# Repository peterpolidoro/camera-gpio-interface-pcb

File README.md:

# camera-gpio-interface-pcb

Interface board for the three FLIR Blackfly S cameras in the Janelia Dudman lab
joystick rig: pluggable screw-terminal camera connectors, two BNC inputs from
the pyControl breakout, four 3.3 V BNC outputs to a Neuropixels OneBox, an
InstrumentPort-Digital-50 with every camera line tapped, and USB power. No
MCU, no firmware, no configuration jumpers.

**Status, October 2026:** v1.0 is the fabricated revision. Five assembled
boards were ordered from JLCPCB on 2026-09-26
([fabrication log](docs/fabrication-log.md)), and one is installed in the
rig, wired to the three cameras, the pyControl breakout and the OneBox. Bench
results per board go in [the bring-up log](docs/bringup-log.md).

## The Board

The block below is written by `make docs` from the KiCad sources: renders, key
dimensions, and links to the schematic, BOM, STEP model and enclosure geometry.
Do not edit between the markers; run `make docs` instead.

<!-- BEGIN GENERATED BOARD DOCUMENTATION -->
<!-- Generated by orb-weaver-kicad-docs. Edits between these markers are lost. -->

More views, including both elevations, are in [the generated documentation](docs/generated/README.md).

The documentation site, with the board turning and its design blocks clickable: [https://peterpolidoro.github.io/camera-gpio-interface-pcb/](https://peterpolidoro.github.io/camera-gpio-interface-pcb/).

| Property | Value |
| --- | --- |
| Outline | 100.0 × 60.0 mm, 5.0 mm corner radius |
| Thickness | 1.6 mm |
| Copper layers | 4 |
| Mounting holes | 4 × 3.2 mm |
| Connectors and controls | 11 |
| Bill of materials | 26 distinct parts, 151 placements |

### Documents

| Document | File |
| --- | --- |
| Schematic, all sheets, PDF | [camera-gpio-interface-pcb-schematic.pdf](docs/generated/schematic/camera-gpio-interface-pcb-schematic.pdf) |
| Schematic sheets, SVG (11) | [schematic/](docs/generated/schematic/) |
| Schematic, instance overviews and details, PDF | [Review booklet](docs/generated/schematic/camera-gpio-interface-pcb-schematic-review.pdf) |
| Design blocks placed (7), one page each | [blocks/README.md](docs/generated/blocks/README.md) |
| Board view: the model and the top render with the design blocks numbered | [board-view.md](docs/generated/board-view.md) |
| Subsystem sheets (3), from their recipes | [subsystems/README.md](docs/generated/subsystems/README.md) |
| Assembly view, top | [assembly-top.svg](docs/generated/layout/assembly-top.svg) |
| Assembly view, bottom | [assembly-bottom.svg](docs/generated/layout/assembly-bottom.svg) |
| Assembled board, STEP, for FreeCAD | [camera-gpio-interface-pcb-assembled.step](docs/generated/3d/camera-gpio-interface-pcb-assembled.step) |
| Assembled board, glTF, for a viewer (the library's materials written in) | [camera-gpio-interface-pcb.glb](docs/generated/3d/camera-gpio-interface-pcb.glb) |
| Bill of materials | [table](docs/generated/bom/camera-gpio-interface-pcb-bom.md) · [CSV](docs/generated/bom/camera-gpio-interface-pcb-bom.csv) |
| Outline and mounting holes, dimensioned drawing | [SVG](docs/generated/mechanical/board-dimensions.svg) · [PDF](docs/generated/mechanical/board-dimensions.pdf) · [PNG](docs/generated/mechanical/board-dimensions.png) |
| Board dimensions and stackup | [board-dimensions.md](docs/generated/mechanical/board-dimensions.md) |
| Board geometry, machine readable | [board-geometry.json](docs/generated/mechanical/board-geometry.json) |
| Mounting holes | [mounting-holes.csv](docs/generated/mechanical/mounting-holes.csv) |
| Connector locations | [connectors.csv](docs/generated/mechanical/connectors.csv) |

### Enclosure Reference

Millimetres from the **centre of the board outline**, X right and Y up,
looking at the top of the board. Extents are the part's courtyard, which is
what a panel cutout has to clear. Full tables in [board-dimensions.md](docs/generated/mechanical/board-dimensions.md).

The outline and the mounting holes dimensioned, as KiCad draws them: [SVG](docs/generated/mechanical/board-dimensions.svg) · [PDF](docs/generated/mechanical/board-dimensions.pdf); the cross is the centre the tables measure from.

**Mounting holes**

| Ref | X (mm) | Y (mm) | Drill (mm) |
| --- | --- | --- | --- |
| H101 | -45.0 | 25.0 | 3.2 |
| H102 | 45.0 | 25.0 | 3.2 |
| H103 | 45.0 | -25.0 | 3.2 |
| H104 | -45.0 | -25.0 | 3.2 |

**Connectors and controls**

| Ref | Part | X (mm) | Y (mm) | Rot | Extent X (mm) | Extent Y (mm) |
| --- | --- | --- | --- | --- | --- | --- |
| J301 | HL-BNC-KHDA | -24.0 | -23.0 | 0.0 | -30.5 to -17.5 | -29.5 to -16.5 |
| J302 | HL-BNC-KHDA | 0.0 | -23.0 | 0.0 | -6.5 to 6.5 | -29.5 to -16.5 |
| J401 | HL-BNC-KHDA | 24.0 | -23.0 | 0.0 | 17.5 to 30.5 | -29.5 to -16.5 |
| J402 | HL-BNC-KHDA | -24.0 | 1.0 | 0.0 | -30.5 to -17.5 | -5.5 to 7.5 |
| J403 | HL-BNC-KHDA | 0.0 | 1.0 | 0.0 | -6.5 to 6.5 | -5.5 to 7.5 |
| J404 | HL-BNC-KHDA | 24.0 | 1.0 | 0.0 | 17.5 to 30.5 | -5.5 to 7.5 |
| J501 | FH12-50S-0.5SVA(54) | 44.0 | -4.0 | 270.0 | 41.2 to 46.8 | -18.75 to 10.75 |
| J701 | TBH-1x06-3.5mm | -25.0 | 24.0 | 180.0 | -36.7 to -13.3 | 19.25 to 27.5 |
| J901 | USB-C | -44.0 | 1.0 | 90.0 | -46.31 to -41.69 | -4.05 to 6.05 |
| J1201 | TBH-1x06-3.5mm | 0.0 | 24.0 | 180.0 | -11.7 to 11.7 | 19.25 to 27.5 |
| J1401 | TBH-1x06-3.5mm | 25.0 | 24.0 | 180.0 | 13.3 to 36.7 | 19.25 to 27.5 |

<!-- END GENERATED BOARD DOCUMENTATION -->

## Documents

- [Interface map](docs/interface-map.md): what each connector and instrument-port channel carries
- [Rev 0 plan](docs/rev0-plan.md): the design record
- [Fabrication log](docs/fabrication-log.md): what was ordered, from which commit, with which package hashes
- [Bring-up log](docs/bringup-log.md): bench results per board serial
- [Generated board documentation](docs/generated/README.md): schematic PDF and SVGs, renders, STEP and glTF, BOM, enclosure geometry and the dimensioned outline drawing, one page per placed design block and per subsystem sheet, rebuilt from the KiCad sources
- [The documentation site](https://peterpolidoro.github.io/camera-gpio-interface-pcb/): the same pages with the board turning and its design blocks clickable

## Fabrication

The v1.0 boards were ordered assembled from JLCPCB from the package built at
commit `5ddb425`. [The fabrication log](docs/fabrication-log.md) records the
commit, the source hashes and the hash of every file JLCPCB received.
[fab/camera-gpio-interface-pcb/](fab/camera-gpio-interface-pcb/) holds the
package rebuilt from the same sources on 2026-10-12: upload
`camera-gpio-interface-pcb-jlcpcb.zip`, `jlcpcb-bom.csv` and
`jlcpcb-camera-gpio-interface-pcb-all-pos.csv` to order more boards. The BOM
and placement files are byte-identical to the uploaded ones; the gerbers
differ only by the creation time in their headers. To fabricate elsewhere,
plot the layers and drill files from `kicad/camera-gpio-interface-pcb.kicad_pcb`
in KiCad. JLCPCB's placement rotation differs from KiCad's for some
footprints, so check the assembly preview before confirming an order.

## Related Repositories

- [mouse-joystick-pcb](https://github.com/peterpolidoro/mouse-joystick-pcb): the rig's joystick controller board.
- [mouse-joystick-firm](https://github.com/peterpolidoro/mouse-joystick-firm): its firmware and the pyControl device class.
- [mouse-joysticks-mech](https://github.com/peterpolidoro/mouse-joysticks-mech): the two-joystick mechanical assembly, part by part, with [the atlas site](https://peterpolidoro.github.io/mouse-joysticks-mech/) and the PDF manual of the whole rig.
- [joystick-rig](https://github.com/sourishmukh/joystick-rig): the rig's pyControl tasks, hardware definition and operating notes.

## Development

Opening, editing and fabricating the board needs only KiCad 10; the schematic
and board carry their own copies of every symbol and footprint. The board was
drawn from a shared KiCad library and toolchain, which is needed only to
regenerate `docs/generated/`, the fabrication package or the composed sheets.
[docs/development.md](docs/development.md) describes that toolchain, the
environment, the sibling repositories and the layout record. Agent guidance is
in `AGENTS.md` and `.agents/`.

## License

Hardware design files and documentation are CC-BY-SA-4.0; code and automation
are 3-clause BSD. See [LICENSE](LICENSE).

## Citation

[CITATION.cff](CITATION.cff) carries the citation metadata; GitHub renders it
under "Cite this repository".

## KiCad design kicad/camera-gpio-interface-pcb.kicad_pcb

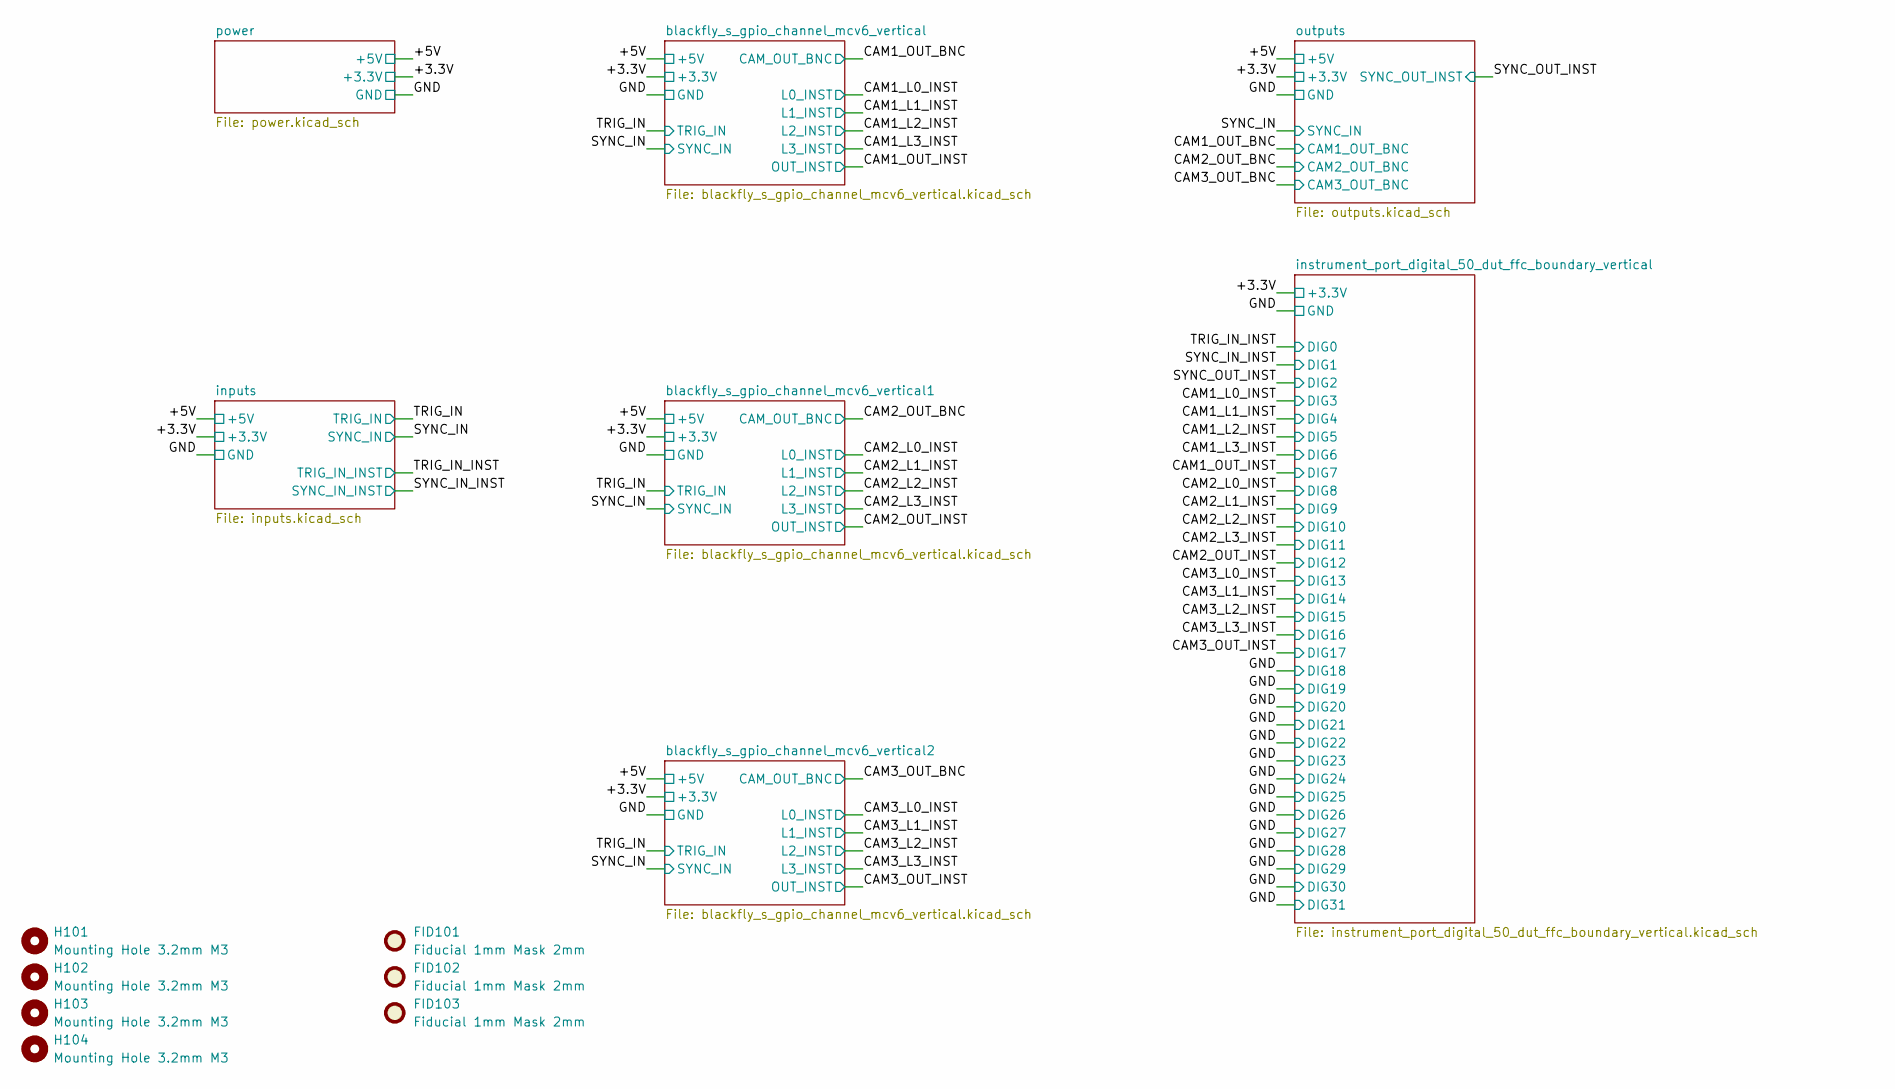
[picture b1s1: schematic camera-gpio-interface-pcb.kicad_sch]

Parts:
FID101, FID102, FID103: Fiducial 1mm Mask 2mm; Fiducial_1mm_Mask2mm
H101, H102, H103, H104: Mounting Hole 3.2mm M3; MountingHole_3.2mm_M3

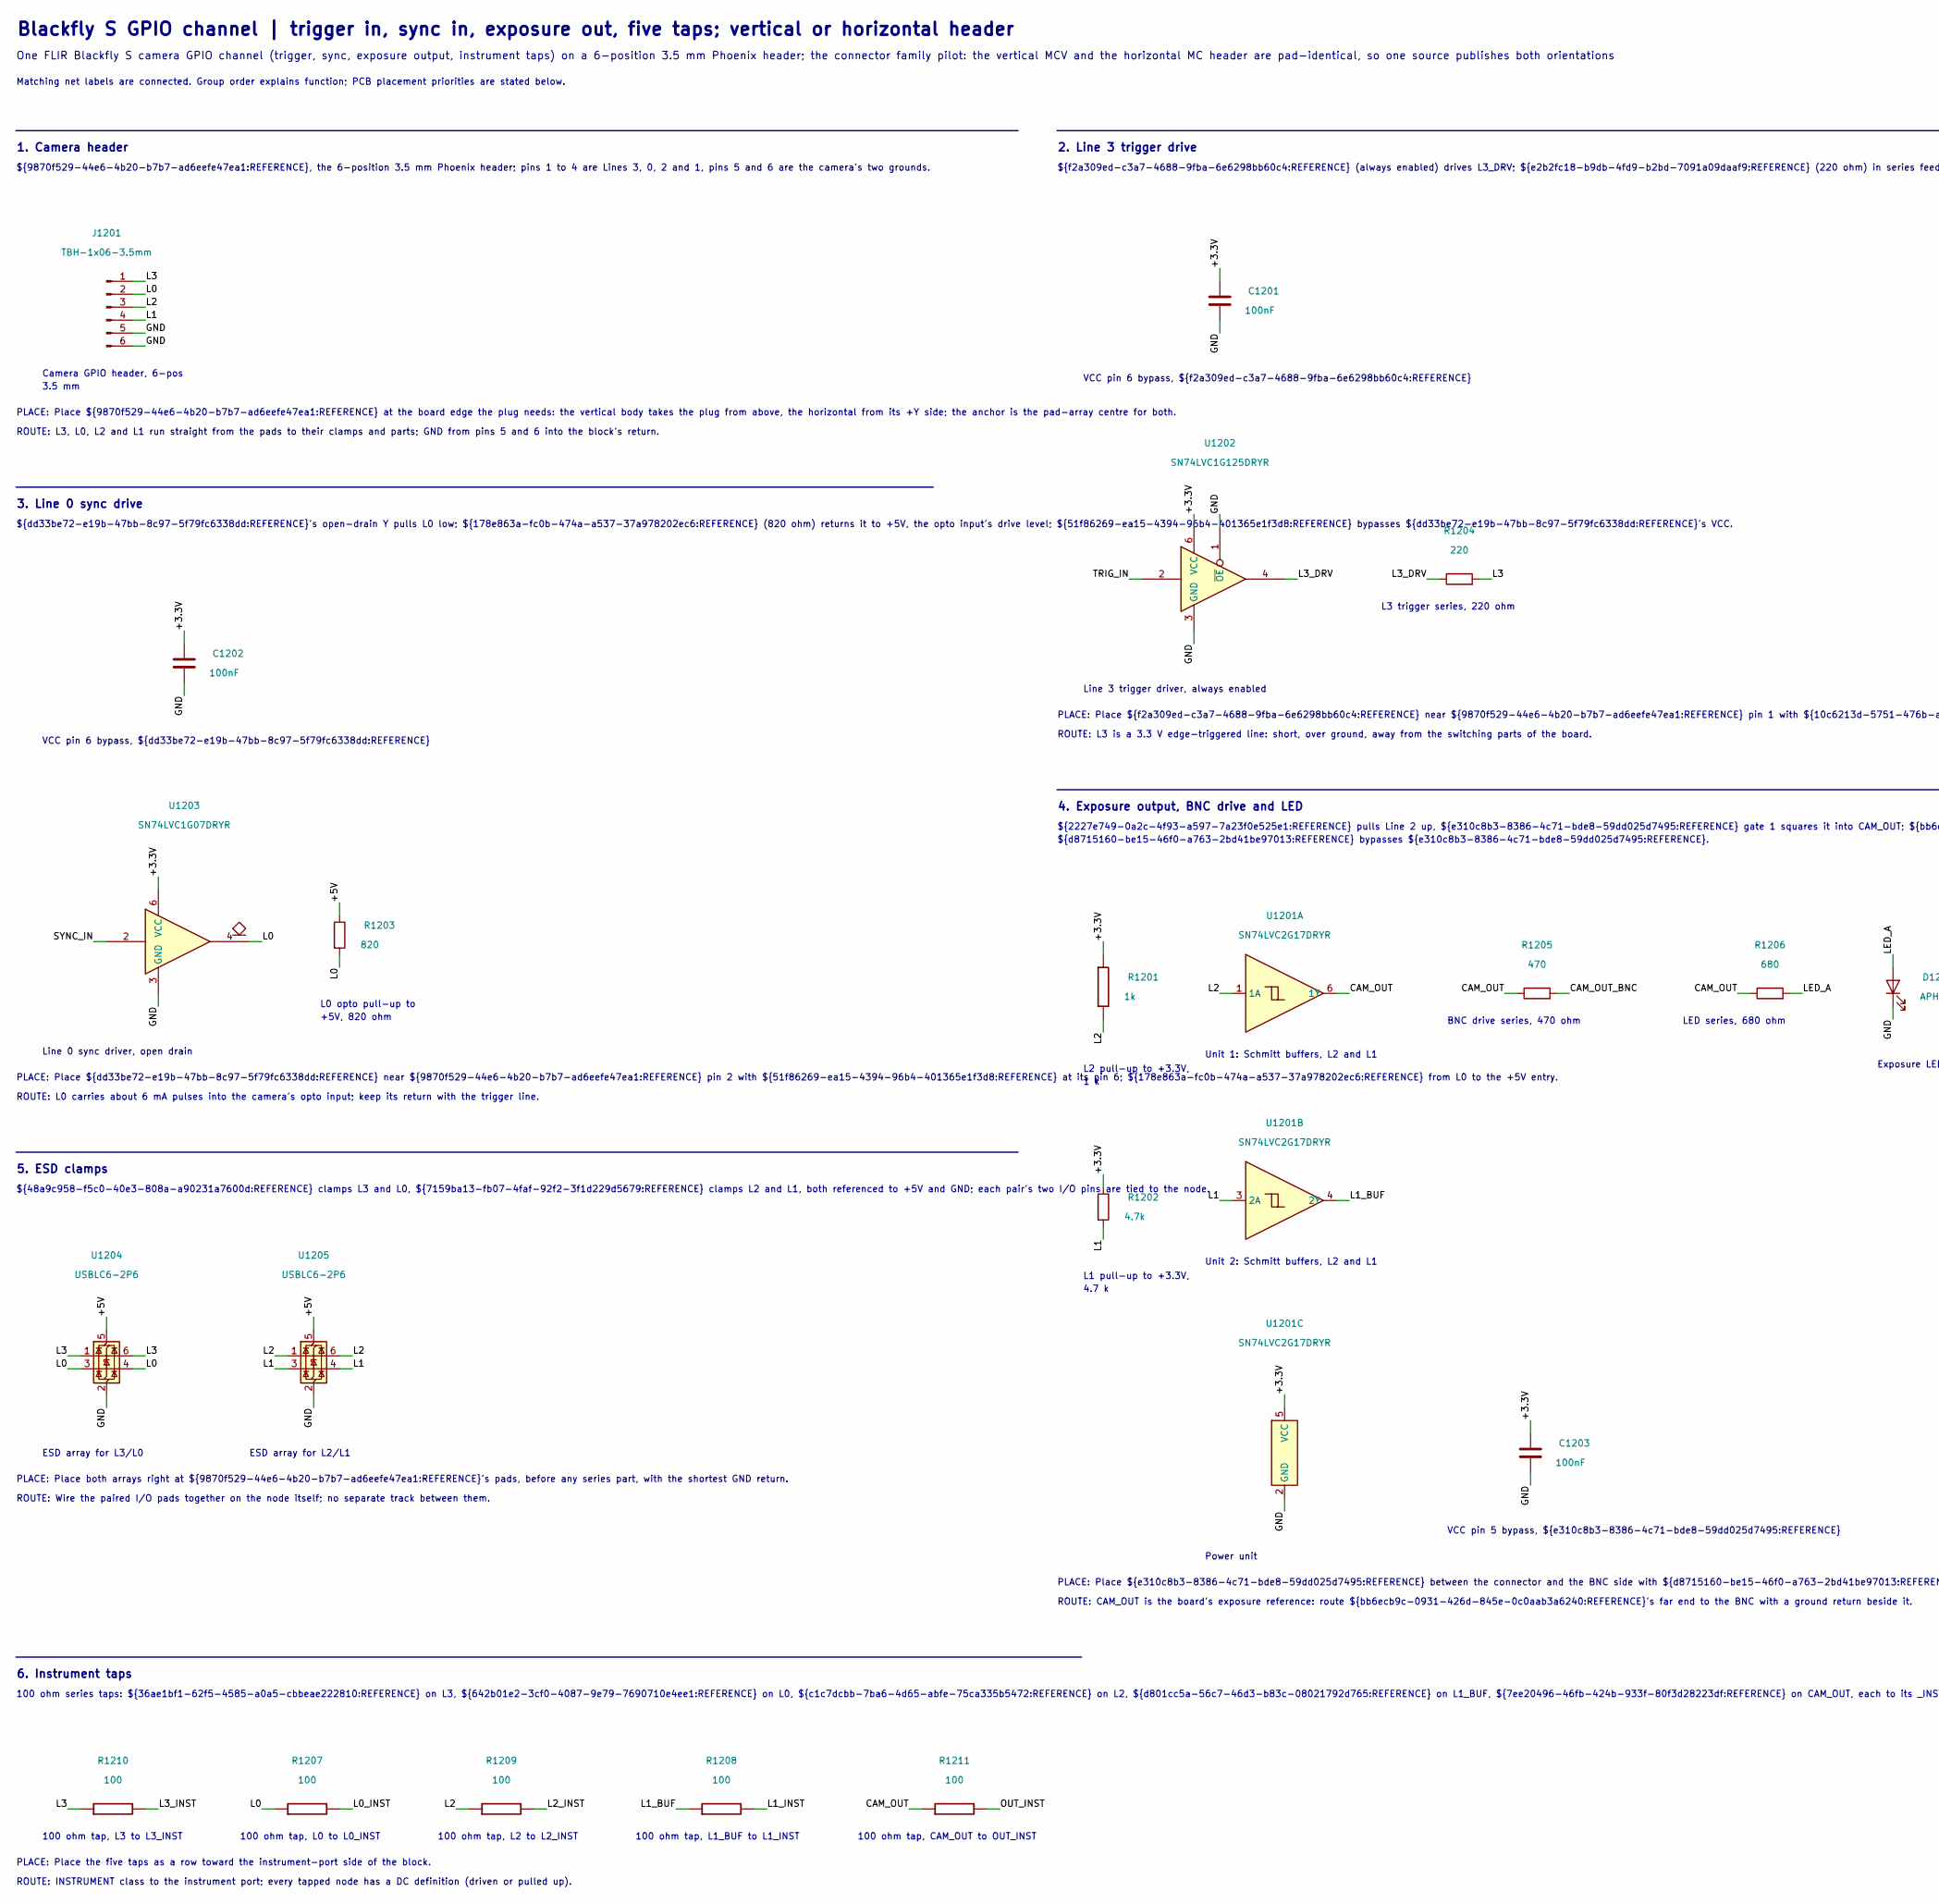
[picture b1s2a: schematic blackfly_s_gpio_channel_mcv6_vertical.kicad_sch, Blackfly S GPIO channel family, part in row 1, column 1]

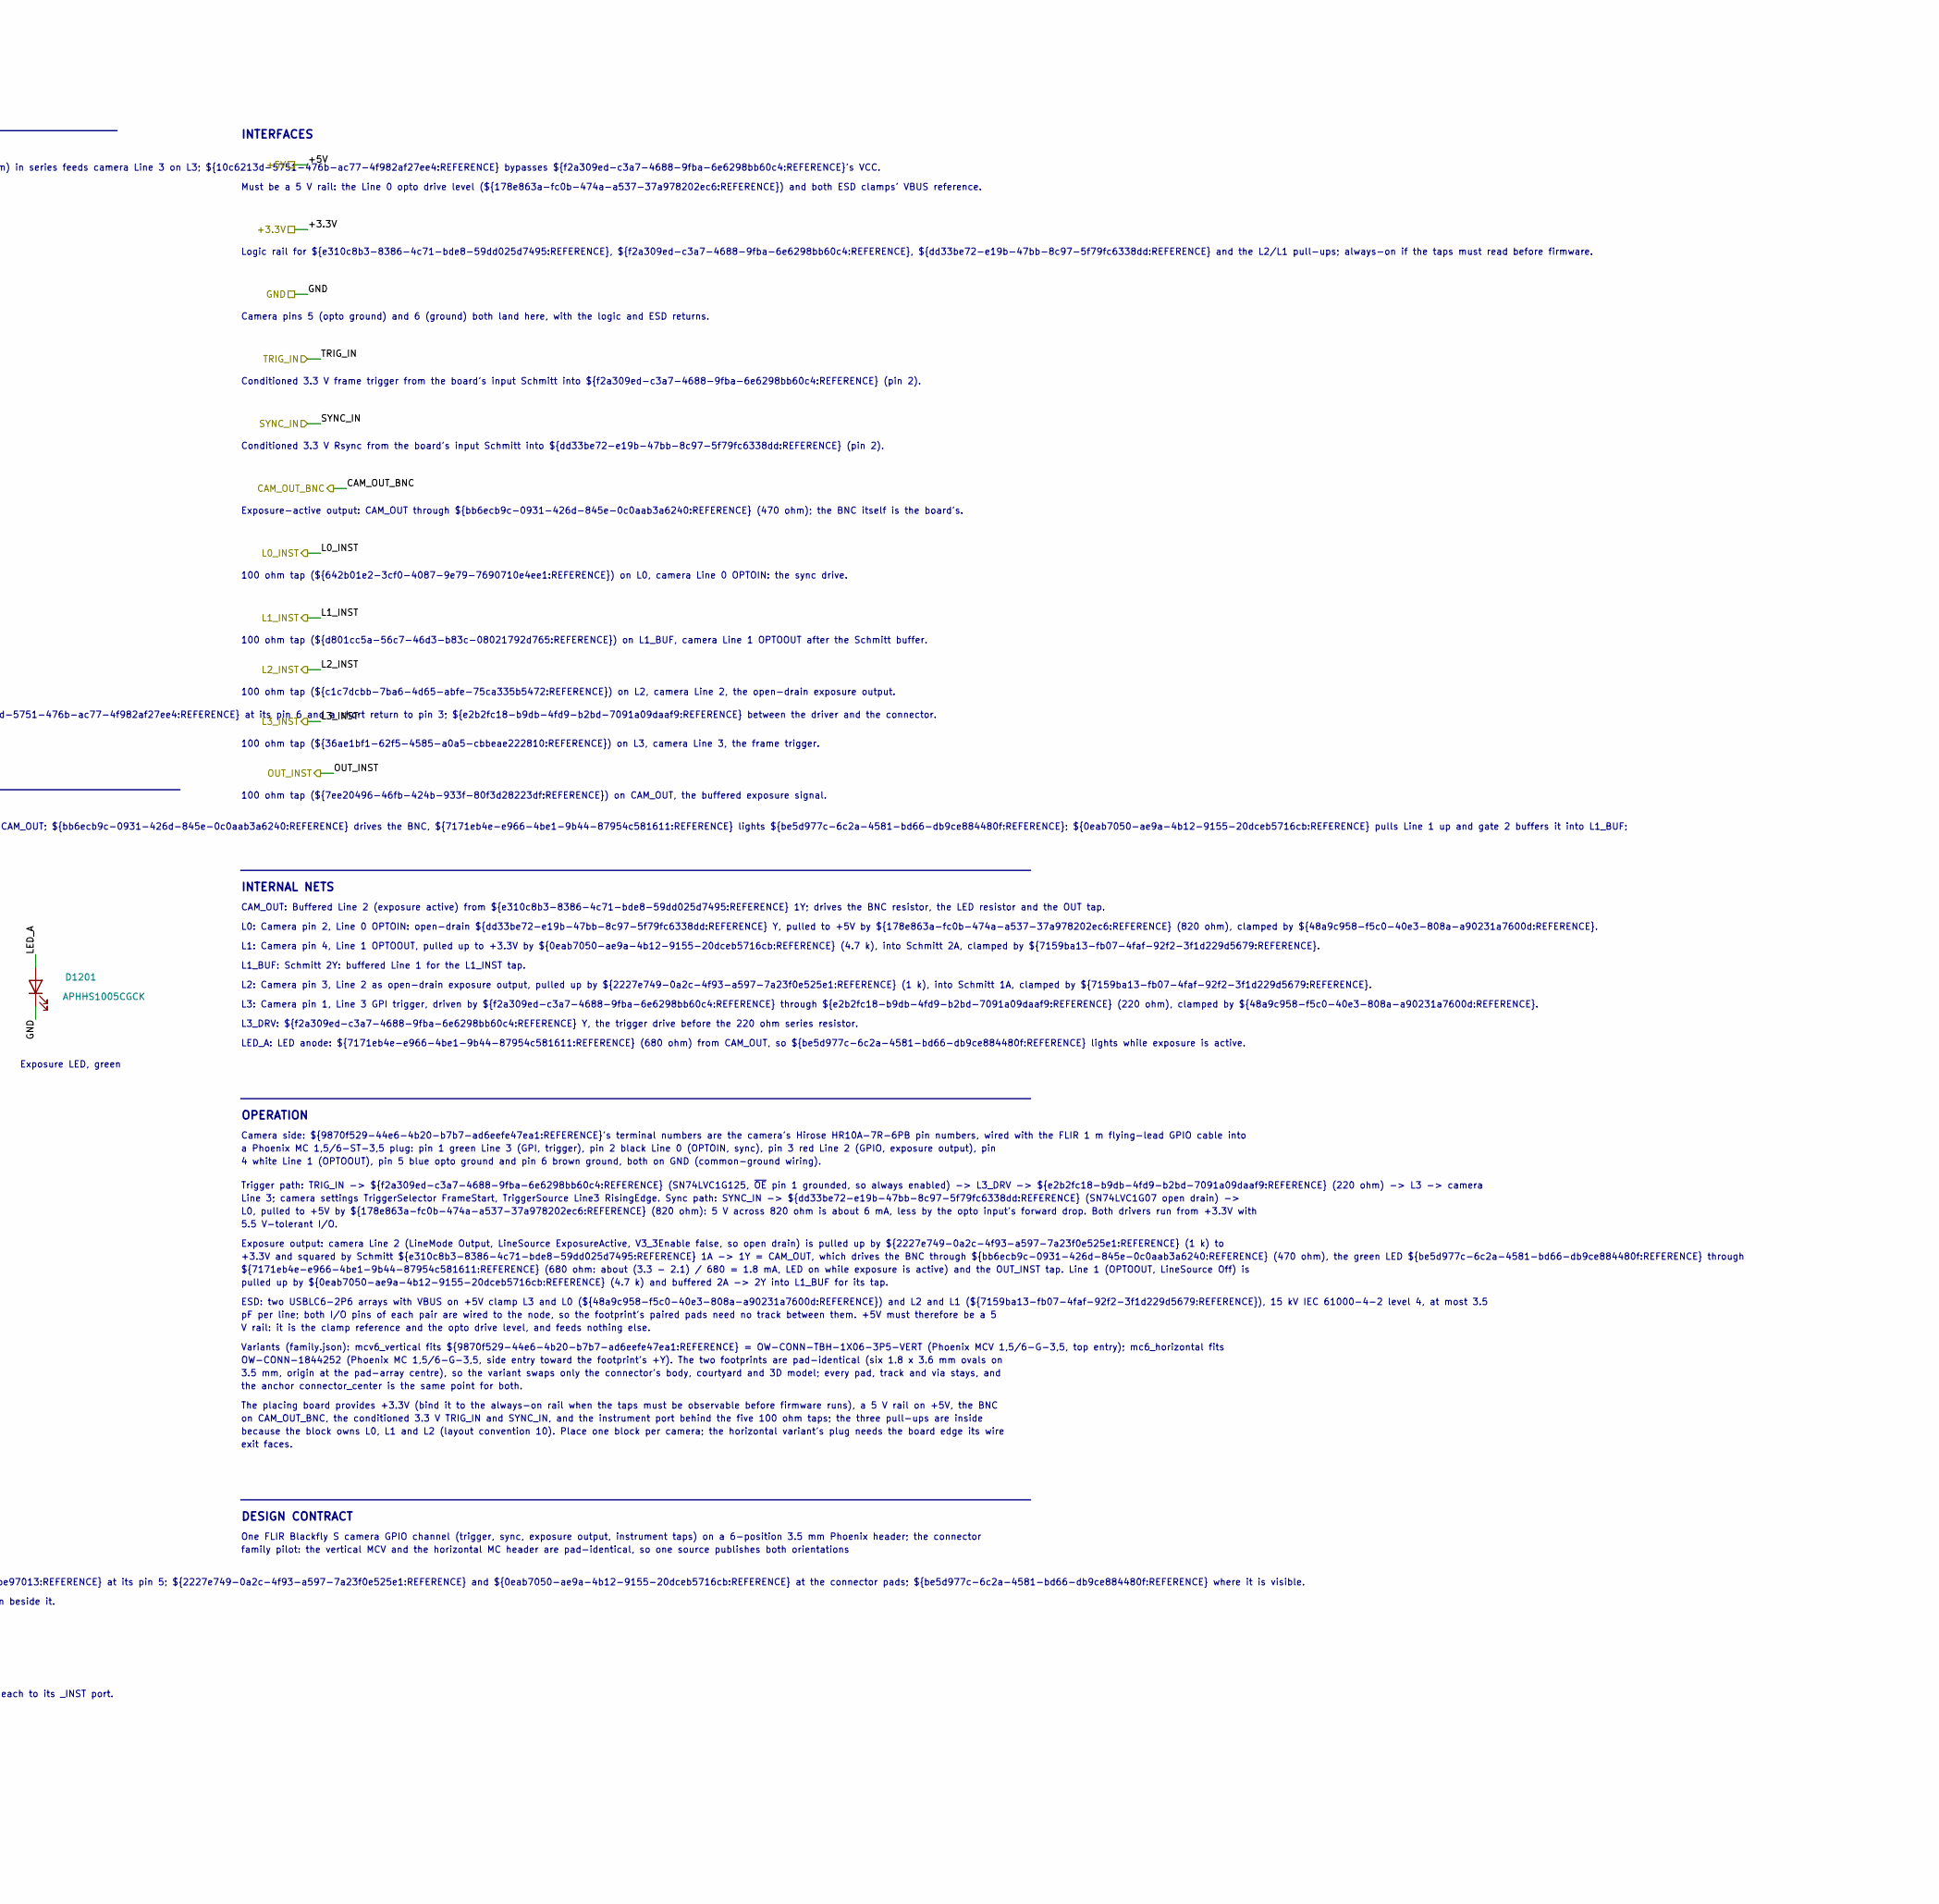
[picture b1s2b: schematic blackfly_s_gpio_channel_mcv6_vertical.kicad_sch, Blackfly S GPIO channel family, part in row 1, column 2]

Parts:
C1201, C1202, C1203: 100nF; C_0402_1005Metric; PartID sym_orb_weaver_passives_c_0_1uf_100v_04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
D1201: APHHS1005CGCK; LED_0402-1005_KNB; PartID sym_orb_weaver_misc_led_knb_20ma_grn_2_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
J1201: TBH-1x06-3.5mm; PhoenixContact_MCV_1,5_6-G-3.5_1x06_P3.50mm_Vertical; PartID sym_orb_weaver_connectors_conn_01x06_p3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
R1201: 1k; R_0402_1005Metric; PartID sym_orb_weaver_passives_r_1k_0402
R1202: 4.7k; R_0402_1005Metric; PartID sym_orb_weaver_passives_r_4_7k_0402
R1203: 820; R_0402_1005Metric; PartID mpn_frc0402f8200ts_0402
R1204: 220; R_0603_1608Metric; PartID mpn_0603waf2200t5e_0603
R1205: 470; R_0603_1608Metric; PartID mpn_0603waf4700t5e_0603
R1206: 680; R_0402_1005Metric; PartID mpn_rc0402fr_07680rl_0402
R1207, R1208, R1209, R1210, R1211: 100; R_0402_1005Metric; PartID sym_orb_weaver_passives_r_100_0402
U1201: SN74LVC2G17DRYR; DRY6; PartID sym_orb_weaver_misc_buffer_74lvc2g17dryr
U1202: SN74LVC1G125DRYR; DRY6; PartID sym_orb_weaver_misc_buffer_74lvc1g125dr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
U1203: SN74LVC1G07DRYR; DRY6; PartID sym_orb_weaver_misc_buffer_74lvc1g07dryr
U1204, U1205: USBLC6-2P6; USBLC6-2P6_SOT-666; PartID mpn_usblc6_2p6_sot_666_6

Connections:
/+3.3V: C1201.1, C1202.1, C1203.1, R1201.1, R1202.1, U1201.5 (VCC), U1202.6 (VCC), U1203.6 (VCC); also elsewhere on the board
/+5V: R1203.1, U1204.5 (VBUS), U1205.5 (VBUS); also elsewhere on the board
/CAM2_L0_INST: R1207.2; also elsewhere on the board
/CAM2_L1_INST: R1208.2; also elsewhere on the board
/CAM2_L2_INST: R1209.2; also elsewhere on the board
/CAM2_L3_INST: R1210.2; also elsewhere on the board
/CAM2_OUT_BNC: R1205.2; also elsewhere on the board
/CAM2_OUT_INST: R1211.2; also elsewhere on the board
/GND: C1201.2, C1202.2, C1203.2, D1201.1 (K), J1201.5, J1201.6, U1201.2 (GND), U1202.1 (~OE), U1202.3 (GND), U1203.3 (GND), U1204.2 (GND), U1205.2 (GND); also elsewhere on the board
/SYNC_IN: U1203.2; also elsewhere on the board
/TRIG_IN: U1202.2; also elsewhere on the board
/blackfly_s_gpio_channel_mcv6_vertical1/CAM_OUT: R1205.1, R1206.1, R1211.1, U1201.6 (1Y)
/blackfly_s_gpio_channel_mcv6_vertical1/L0: J1201.2, R1203.2, R1207.1, U1203.4, U1204.3 (I/O2), U1204.4 (I/O2)
/blackfly_s_gpio_channel_mcv6_vertical1/L1: J1201.4, R1202.2, U1201.3 (2A), U1205.3 (I/O2), U1205.4 (I/O2)
/blackfly_s_gpio_channel_mcv6_vertical1/L1_BUF: R1208.1, U1201.4 (2Y)
/blackfly_s_gpio_channel_mcv6_vertical1/L2: J1201.3, R1201.2, R1209.1, U1201.1 (1A), U1205.1 (I/O1), U1205.6 (I/O1)
/blackfly_s_gpio_channel_mcv6_vertical1/L3: J1201.1, R1204.2, R1210.1, U1204.1 (I/O1), U1204.6 (I/O1)
/blackfly_s_gpio_channel_mcv6_vertical1/L3_DRV: R1204.1, U1202.4
/blackfly_s_gpio_channel_mcv6_vertical1/LED_A: D1201.2 (A), R1206.2

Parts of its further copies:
C701, C702, C703, C1401, C1402, C1403: 100nF; C_0402_1005Metric; PartID sym_orb_weaver_passives_c_0_1uf_100v_04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
D701, D1401: APHHS1005CGCK; LED_0402-1005_KNB; PartID sym_orb_weaver_misc_led_knb_20ma_grn_2_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
J701, J1401: TBH-1x06-3.5mm; PhoenixContact_MCV_1,5_6-G-3.5_1x06_P3.50mm_Vertical; PartID sym_orb_weaver_connectors_conn_01x06_p3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
R701, R1401: 1k; R_0402_1005Metric; PartID sym_orb_weaver_passives_r_1k_0402
R702, R1402: 4.7k; R_0402_1005Metric; PartID sym_orb_weaver_passives_r_4_7k_0402
R703, R1403: 820; R_0402_1005Metric; PartID mpn_frc0402f8200ts_0402
R704, R1404: 220; R_0603_1608Metric; PartID mpn_0603waf2200t5e_0603
R705, R1405: 470; R_0603_1608Metric; PartID mpn_0603waf4700t5e_0603
R706, R1406: 680; R_0402_1005Metric; PartID mpn_rc0402fr_07680rl_0402
R707, R708, R709, R710, R711, R1407, R1408, R1409, R1410, R1411: 100; R_0402_1005Metric; PartID sym_orb_weaver_passives_r_100_0402
U701, U1401: SN74LVC2G17DRYR; DRY6; PartID sym_orb_weaver_misc_buffer_74lvc2g17dryr
U702, U1402: SN74LVC1G125DRYR; DRY6; PartID sym_orb_weaver_misc_buffer_74lvc1g125dr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
U703, U1403: SN74LVC1G07DRYR; DRY6; PartID sym_orb_weaver_misc_buffer_74lvc1g07dryr
U704, U705, U1404, U1405: USBLC6-2P6; USBLC6-2P6_SOT-666; PartID mpn_usblc6_2p6_sot_666_6

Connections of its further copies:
/+3.3V: C701.1, C702.1, C703.1, C1401.1, C1402.1, C1403.1, R701.1, R702.1, R1401.1, R1402.1, U701.5 (VCC), U702.6 (VCC), U703.6 (VCC), U1401.5 (VCC), U1402.6 (VCC), U1403.6 (VCC); also elsewhere on the board
/+5V: R703.1, R1403.1, U704.5 (VBUS), U705.5 (VBUS), U1404.5 (VBUS), U1405.5 (VBUS); also elsewhere on the board
/CAM1_L0_INST: R707.2; also elsewhere on the board
/CAM1_L1_INST: R708.2; also elsewhere on the board
/CAM1_L2_INST: R709.2; also elsewhere on the board
/CAM1_L3_INST: R710.2; also elsewhere on the board
/CAM1_OUT_BNC: R705.2; also elsewhere on the board
/CAM1_OUT_INST: R711.2; also elsewhere on the board
/CAM3_L0_INST: R1407.2; also elsewhere on the board
/CAM3_L1_INST: R1408.2; also elsewhere on the board
/CAM3_L2_INST: R1409.2; also elsewhere on the board
/CAM3_L3_INST: R1410.2; also elsewhere on the board
/CAM3_OUT_BNC: R1405.2; also elsewhere on the board
/CAM3_OUT_INST: R1411.2; also elsewhere on the board
/GND: C701.2, C702.2, C703.2, C1401.2, C1402.2, C1403.2, D701.1 (K), D1401.1 (K), J701.5, J701.6, J1401.5, J1401.6, U701.2 (GND), U702.1 (~OE), U702.3 (GND), U703.3 (GND), U704.2 (GND), U705.2 (GND), U1401.2 (GND), U1402.1 (~OE), U1402.3 (GND), U1403.3 (GND), U1404.2 (GND), U1405.2 (GND); also elsewhere on the board
/SYNC_IN: U703.2, U1403.2; also elsewhere on the board
/TRIG_IN: U702.2, U1402.2; also elsewhere on the board
/blackfly_s_gpio_channel_mcv6_vertical2/CAM_OUT: R1405.1, R1406.1, R1411.1, U1401.6 (1Y)
/blackfly_s_gpio_channel_mcv6_vertical2/L0: J1401.2, R1403.2, R1407.1, U1403.4, U1404.3 (I/O2), U1404.4 (I/O2)
/blackfly_s_gpio_channel_mcv6_vertical2/L1: J1401.4, R1402.2, U1401.3 (2A), U1405.3 (I/O2), U1405.4 (I/O2)
/blackfly_s_gpio_channel_mcv6_vertical2/L1_BUF: R1408.1, U1401.4 (2Y)
/blackfly_s_gpio_channel_mcv6_vertical2/L2: J1401.3, R1401.2, R1409.1, U1401.1 (1A), U1405.1 (I/O1), U1405.6 (I/O1)
/blackfly_s_gpio_channel_mcv6_vertical2/L3: J1401.1, R1404.2, R1410.1, U1404.1 (I/O1), U1404.6 (I/O1)
/blackfly_s_gpio_channel_mcv6_vertical2/L3_DRV: R1404.1, U1402.4
/blackfly_s_gpio_channel_mcv6_vertical2/LED_A: D1401.2 (A), R1406.2
/blackfly_s_gpio_channel_mcv6_vertical/CAM_OUT: R705.1, R706.1, R711.1, U701.6 (1Y)
/blackfly_s_gpio_channel_mcv6_vertical/L0: J701.2, R703.2, R707.1, U703.4, U704.3 (I/O2), U704.4 (I/O2)
/blackfly_s_gpio_channel_mcv6_vertical/L1: J701.4, R702.2, U701.3 (2A), U705.3 (I/O2), U705.4 (I/O2)
/blackfly_s_gpio_channel_mcv6_vertical/L1_BUF: R708.1, U701.4 (2Y)
/blackfly_s_gpio_channel_mcv6_vertical/L2: J701.3, R701.2, R709.1, U701.1 (1A), U705.1 (I/O1), U705.6 (I/O1)
/blackfly_s_gpio_channel_mcv6_vertical/L3: J701.1, R704.2, R710.1, U704.1 (I/O1), U704.6 (I/O1)
/blackfly_s_gpio_channel_mcv6_vertical/L3_DRV: R704.1, U702.4
/blackfly_s_gpio_channel_mcv6_vertical/LED_A: D701.2 (A), R706.2

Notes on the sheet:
Blackfly S GPIO channel | trigger in, sync in, exposure out, five taps; vertical or horizontal header
One FLIR Blackfly S camera GPIO channel (trigger, sync, exposure output, instrument taps) on a 6-position 3.5 mm Phoenix header; the connector family pilot: the vertical MCV and the horizontal MC header are pad-identical, so one source publishes both orientations
Matching net labels are connected. Group order explains function; PCB placement priorities are stated below.
1. Camera header
${9870f529-44e6-4b20-b7b7-ad6eefe47ea1:REFERENCE}, the 6-position 3.5 mm Phoenix header; pins 1 to 4 are Lines 3, 0, 2 and 1, pins 5 and 6 are the camera's two grounds.
Camera GPIO header, 6-pos
3.5 mm
PLACE: Place ${9870f529-44e6-4b20-b7b7-ad6eefe47ea1:REFERENCE} at the board edge the plug needs: the vertical body takes the plug from above, the horizontal from its +Y side; the anchor is the pad-array centre for both.
ROUTE: L3, L0, L2 and L1 run straight from the pads to their clamps and parts; GND from pins 5 and 6 into the block's return.
2. Line 3 trigger drive
${f2a309ed-c3a7-4688-9fba-6e6298bb60c4:REFERENCE} (always enabled) drives L3_DRV; ${e2b2fc18-b9db-4fd9-b2bd-7091a09daaf9:REFERENCE} (220 ohm) in series feeds camera Line 3 on L3; ${10c6213d-5751-476b-ac77-4f982af27ee4:REFERENCE} bypasses ${f2a309ed-c3a7-4688-9fba-6e6298bb60c4:REFERENCE}'s VCC.
VCC pin 6 bypass, ${f2a309ed-c3a7-4688-9fba-6e6298bb60c4:REFERENCE}
Line 3 trigger driver, always enabled
L3 trigger series, 220 ohm
PLACE: Place ${f2a309ed-c3a7-4688-9fba-6e6298bb60c4:REFERENCE} near ${9870f529-44e6-4b20-b7b7-ad6eefe47ea1:REFERENCE} pin 1 with ${10c6213d-5751-476b-ac77-4f982af27ee4:REFERENCE} at its pin 6 and a short return to pin 3; ${e2b2fc18-b9db-4fd9-b2bd-7091a09daaf9:REFERENCE} between the driver and the c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
ROUTE: L3 is a 3.3 V edge-triggered line: short, over ground, away from the switching parts of the board.
3. Line 0 sync drive
${dd33be72-e19b-47bb-8c97-5f79fc6338dd:REFERENCE}'s open-drain Y pulls L0 low; ${178e863a-fc0b-474a-a537-37a978202ec6:REFERENCE} (820 ohm) returns it to +5V, the opto input's drive level; ${51f86269-ea15-4394-96b4-401365e1f3d8:REFERENCE} bypasses ${dd33be72-e19b-47bb-8c97-5f79fc6338dd:REFERENCE}'s 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
VCC pin 6 bypass, ${dd33be72-e19b-47bb-8c97-5f79fc6338dd:REFERENCE}
Line 0 sync driver, open drain
L0 opto pull-up to
+5V, 820 ohm
PLACE: Place ${dd33be72-e19b-47bb-8c97-5f79fc6338dd:REFERENCE} near ${9870f529-44e6-4b20-b7b7-ad6eefe47ea1:REFERENCE} pin 2 with ${51f86269-ea15-4394-96b4-401365e1f3d8:REFERENCE} at its pin 6; ${178e863a-fc0b-474a-a537-37a978202ec6:REFERENCE} from L0 to the +5V entry.
ROUTE: L0 carries about 6 mA pulses into the camera's opto input; keep its return with the trigger line.
4. Exposure output, BNC drive and LED
${2227e749-0a2c-4f93-a597-7a23f0e525e1:REFERENCE} pulls Line 2 up, ${e310c8b3-8386-4c71-bde8-59dd025d7495:REFERENCE} gate 1 squares it into CAM_OUT; ${bb6ecb9c-0931-426d-845e-0c0aab3a6240:REFERENCE} drives the BNC, ${7171eb4e-e966-4be1-9b44-87954c581611:REFERENCE} lights ${be5d977c-6c2a-4581-bd66-d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
${d8715160-be15-46f0-a763-2bd41be97013:REFERENCE} bypasses ${e310c8b3-8386-4c71-bde8-59dd025d7495:REFERENCE}.
L2 pull-up to +3.3V,
1 k
Unit 1: Schmitt buffers, L2 and L1
BNC drive series, 470 ohm
LED series, 680 ohm
Exposure LED, green
L1 pull-up to +3.3V,
4.7 k
Unit 2: Schmitt buffers, L2 and L1
Power unit
VCC pin 5 bypass, ${e310c8b3-8386-4c71-bde8-59dd025d7495:REFERENCE}
PLACE: Place ${e310c8b3-8386-4c71-bde8-59dd025d7495:REFERENCE} between the connector and the BNC side with ${d8715160-be15-46f0-a763-2bd41be97013:REFERENCE} at its pin 5; ${2227e749-0a2c-4f93-a597-7a23f0e525e1:REFERENCE} and ${0eab7050-ae9a-4b12-9155-20dceb5716cb:REFERENCE} at the connector pads; $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
ROUTE: CAM_OUT is the board's exposure reference: route ${bb6ecb9c-0931-426d-845e-0c0aab3a6240:REFERENCE}'s far end to the BNC with a ground return beside it.

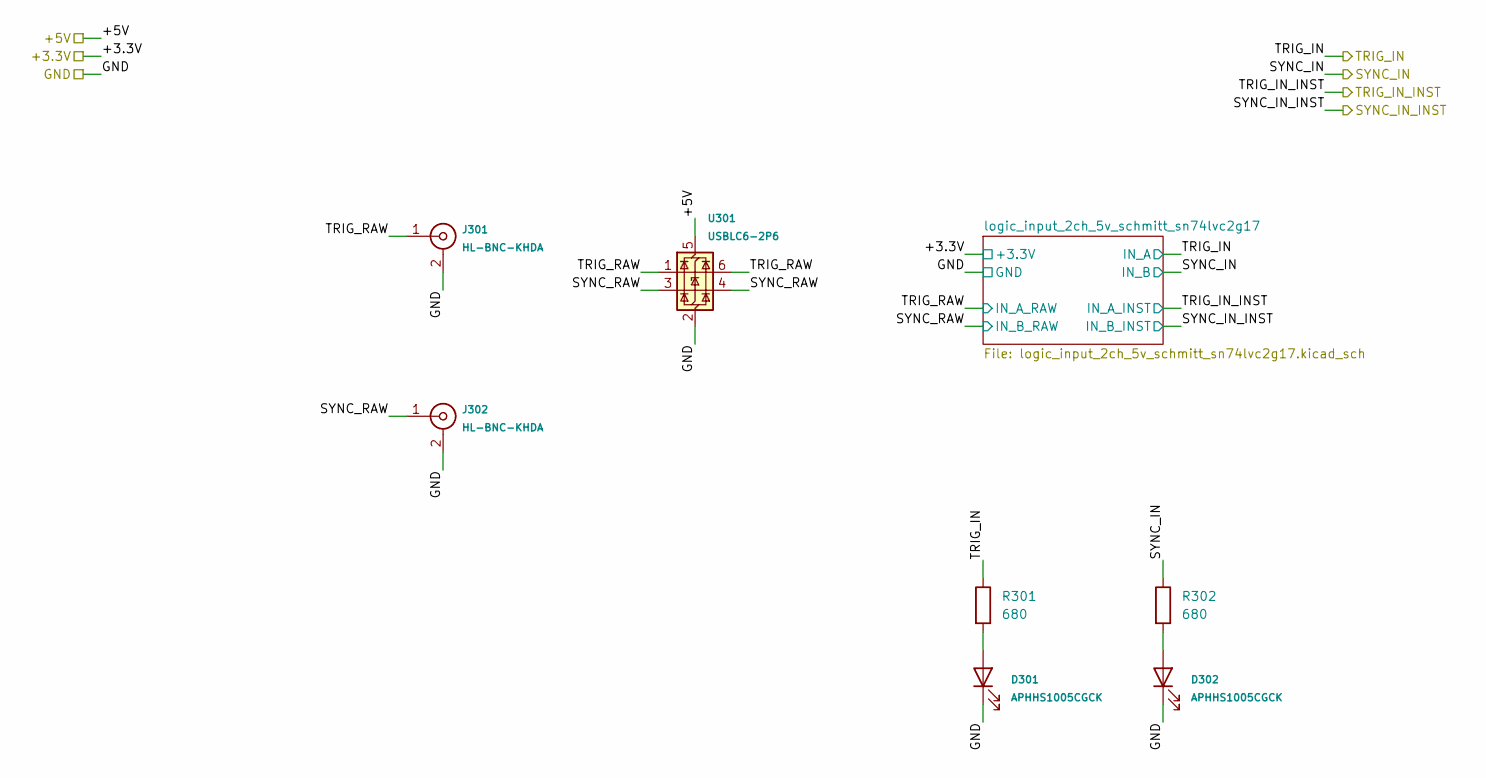
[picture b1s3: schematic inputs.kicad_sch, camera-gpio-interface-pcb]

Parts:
D301, D302: APHHS1005CGCK; LED_0402-1005_KNB; PartID sym_orb_weaver_misc_led_knb_20ma_grn_2_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
J301, J302: HL-BNC-KHDA; CONN_BNC_HL-BNC-KHDA; PartID sym_orb_weaver_connectors_conn_coaxial_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
R301, R302: 680; R_0402_1005Metric; PartID mpn_rc0402fr_07680rl_0402
U301: USBLC6-2P6; USBLC6-2P6_SOT-666; PartID mpn_usblc6_2p6_sot_666_6

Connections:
/+5V: U301.5 (VBUS); also elsewhere on the board
/GND: D301.1 (K), D302.1 (K), J301.2 (Shield), J302.2 (Shield), U301.2 (GND); also elsewhere on the board
/SYNC_IN: R302.1; also elsewhere on the board
/TRIG_IN: R301.1; also elsewhere on the board
/inputs/SYNC_RAW: J302.1 (Signal), U301.3 (I/O2), U301.4 (I/O2); also elsewhere on the board
/inputs/TRIG_RAW: J301.1 (Signal), U301.1 (I/O1), U301.6 (I/O1); also elsewhere on the board
unnamed: D301.2 (A), R301.2
unnamed: D302.2 (A), R302.2

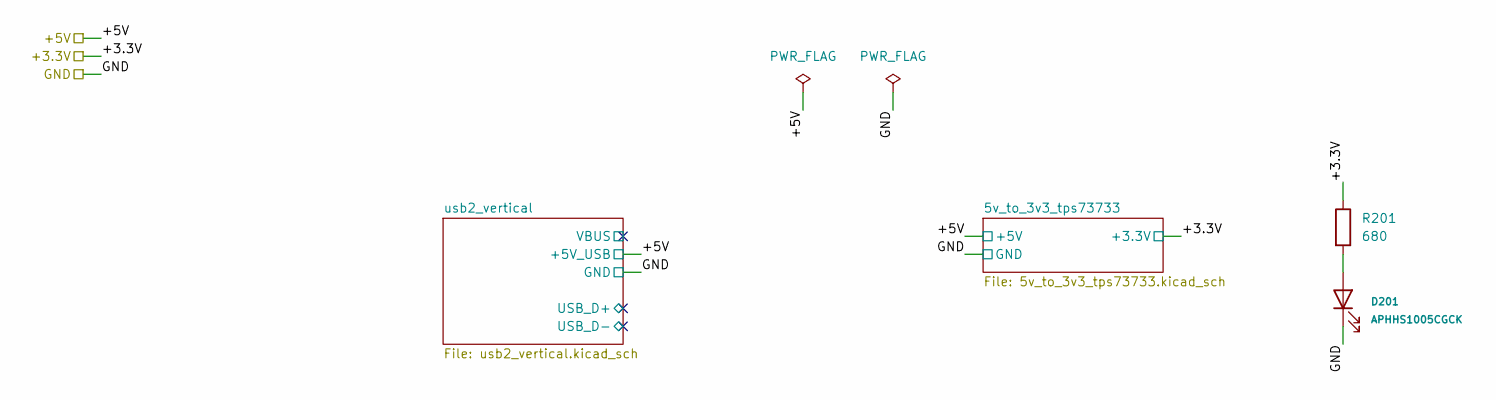
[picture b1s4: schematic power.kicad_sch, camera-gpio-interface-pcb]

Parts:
D201: APHHS1005CGCK; LED_0402-1005_KNB; PartID sym_orb_weaver_misc_led_knb_20ma_grn_2_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
R201: 680; R_0402_1005Metric; PartID mpn_rc0402fr_07680rl_0402

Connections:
/+3.3V: R201.1; also elsewhere on the board
/GND: D201.1 (K); also elsewhere on the board
unnamed: D201.2 (A), R201.2
